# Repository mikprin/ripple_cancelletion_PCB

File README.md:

# repo for PCB's

Cloning this repo

The component libraries for this PCB project are managed as git submodules.

After cloning this repo, you'll need to execute the following commands (inside the repository):

git submodule init

git submodule update

More info on git submodules: https://git-scm.com/book/en/v2/Git-Tools-Submodules

More info on the library management: https://www.youtube.com/watch?v=oXzJFrLo77Y

## ripple_cancelletion_PCB

## 3 & 4 S discharge protection

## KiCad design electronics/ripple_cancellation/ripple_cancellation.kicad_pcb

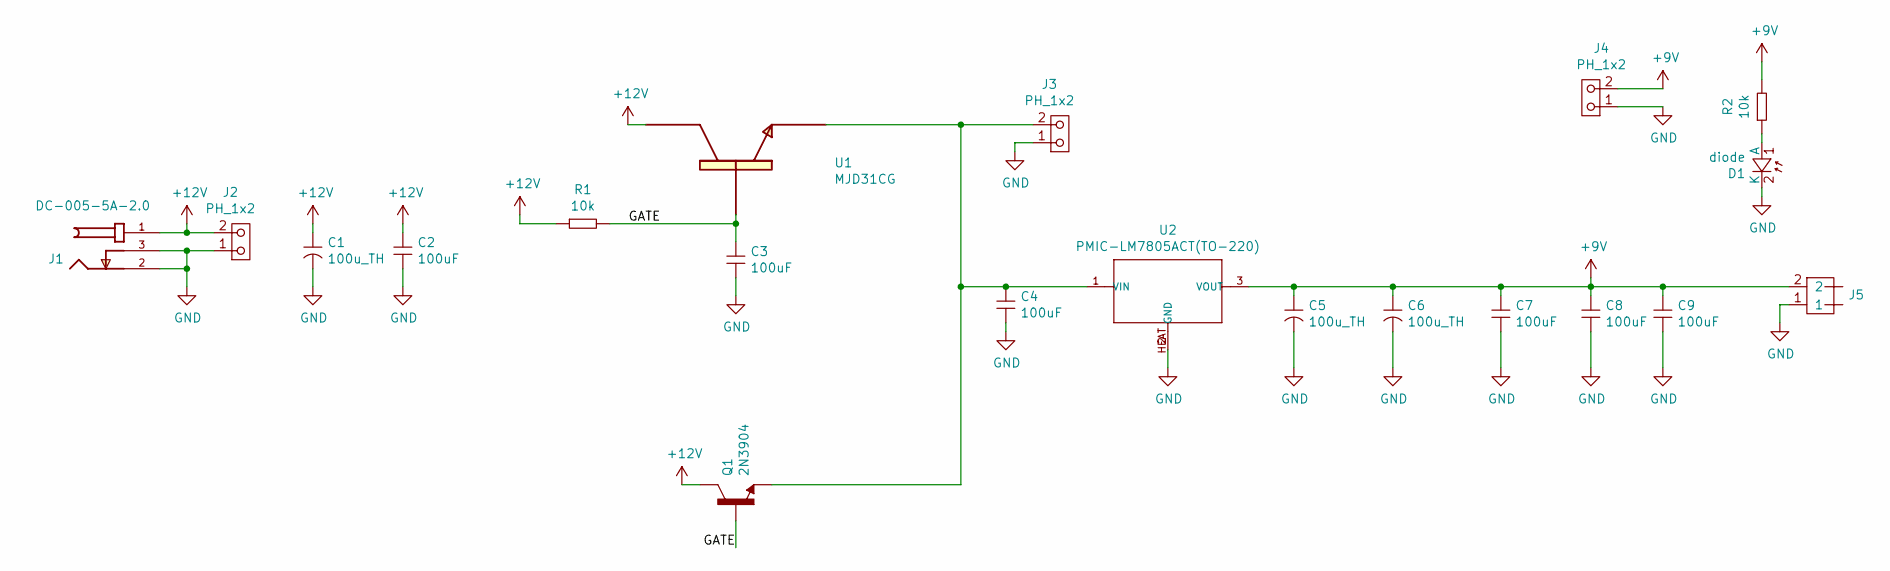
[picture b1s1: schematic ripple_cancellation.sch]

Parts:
C1, C5, C6: 100u_TH; CAP-EL-RADIAL-6.3X12; MFR# RVT1V101M0607
C2, C3, C4, C7, C8, C9: 100uF; 1206_Passive
D1: diode; TH_Diode
J1: DC-005-5A-2.0; XKB_DC-005-5A-2.0; PARTREV A0
J2, J3, J4: PH_1x2; PinHeader_1x2_Generic
J5: 3mm_2pin_solder
Q1: 2N3904; TO92127P495H495-3; PARTREV February 2003
R1, R2: 10k; 0603_Passive
U1: MJD31CG; DPAK229P990X239-3N
U2: PMIC-LM7805ACT(TO-220); TO-220; MPN LM7805ACT

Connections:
+9V: C5.+, C6.+, C7.1, C8.1, C9.1, J4.2, J5.2, R2.2, U2.3 (VOUT)
+12V: C1.+, C2.1, J1.1, J2.2, Q1.3, R1.1, U1.2
/GATE: C3.1, Q1.2, R1.2, U1.1
GND: C1.-, C2.2, C3.2, C4.2, C5.-, C6.-, C7.2, C8.2, C9.2, D1.2 (K), J1.2, J1.3, J2.1, J3.1, J4.1, J5.1, U2.2 (GND), U2.HEAT (GND)
unnamed: C4.1, J3.2, Q1.1, U1.3, U2.1 (VIN)
unnamed: D1.1 (A), R2.1

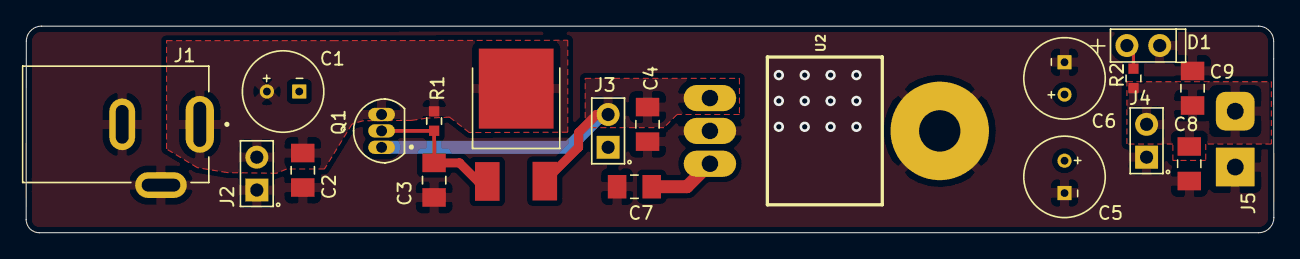
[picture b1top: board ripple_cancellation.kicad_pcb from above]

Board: 2 copper layers, 96.5 x 16.0 mm, 20 parts (0 on the bottom side), 6 nets.

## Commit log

2021-12-17 ini lib
2021-12-20 Пн 20 дек 2021 18:32:38 MSK
2021-12-20 Пн 20 дек 2021 18:34:11 MSK
2021-12-20 new stucture
2021-12-20 README
